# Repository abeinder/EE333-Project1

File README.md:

# EE333-Project1
EE design project for EE 333.

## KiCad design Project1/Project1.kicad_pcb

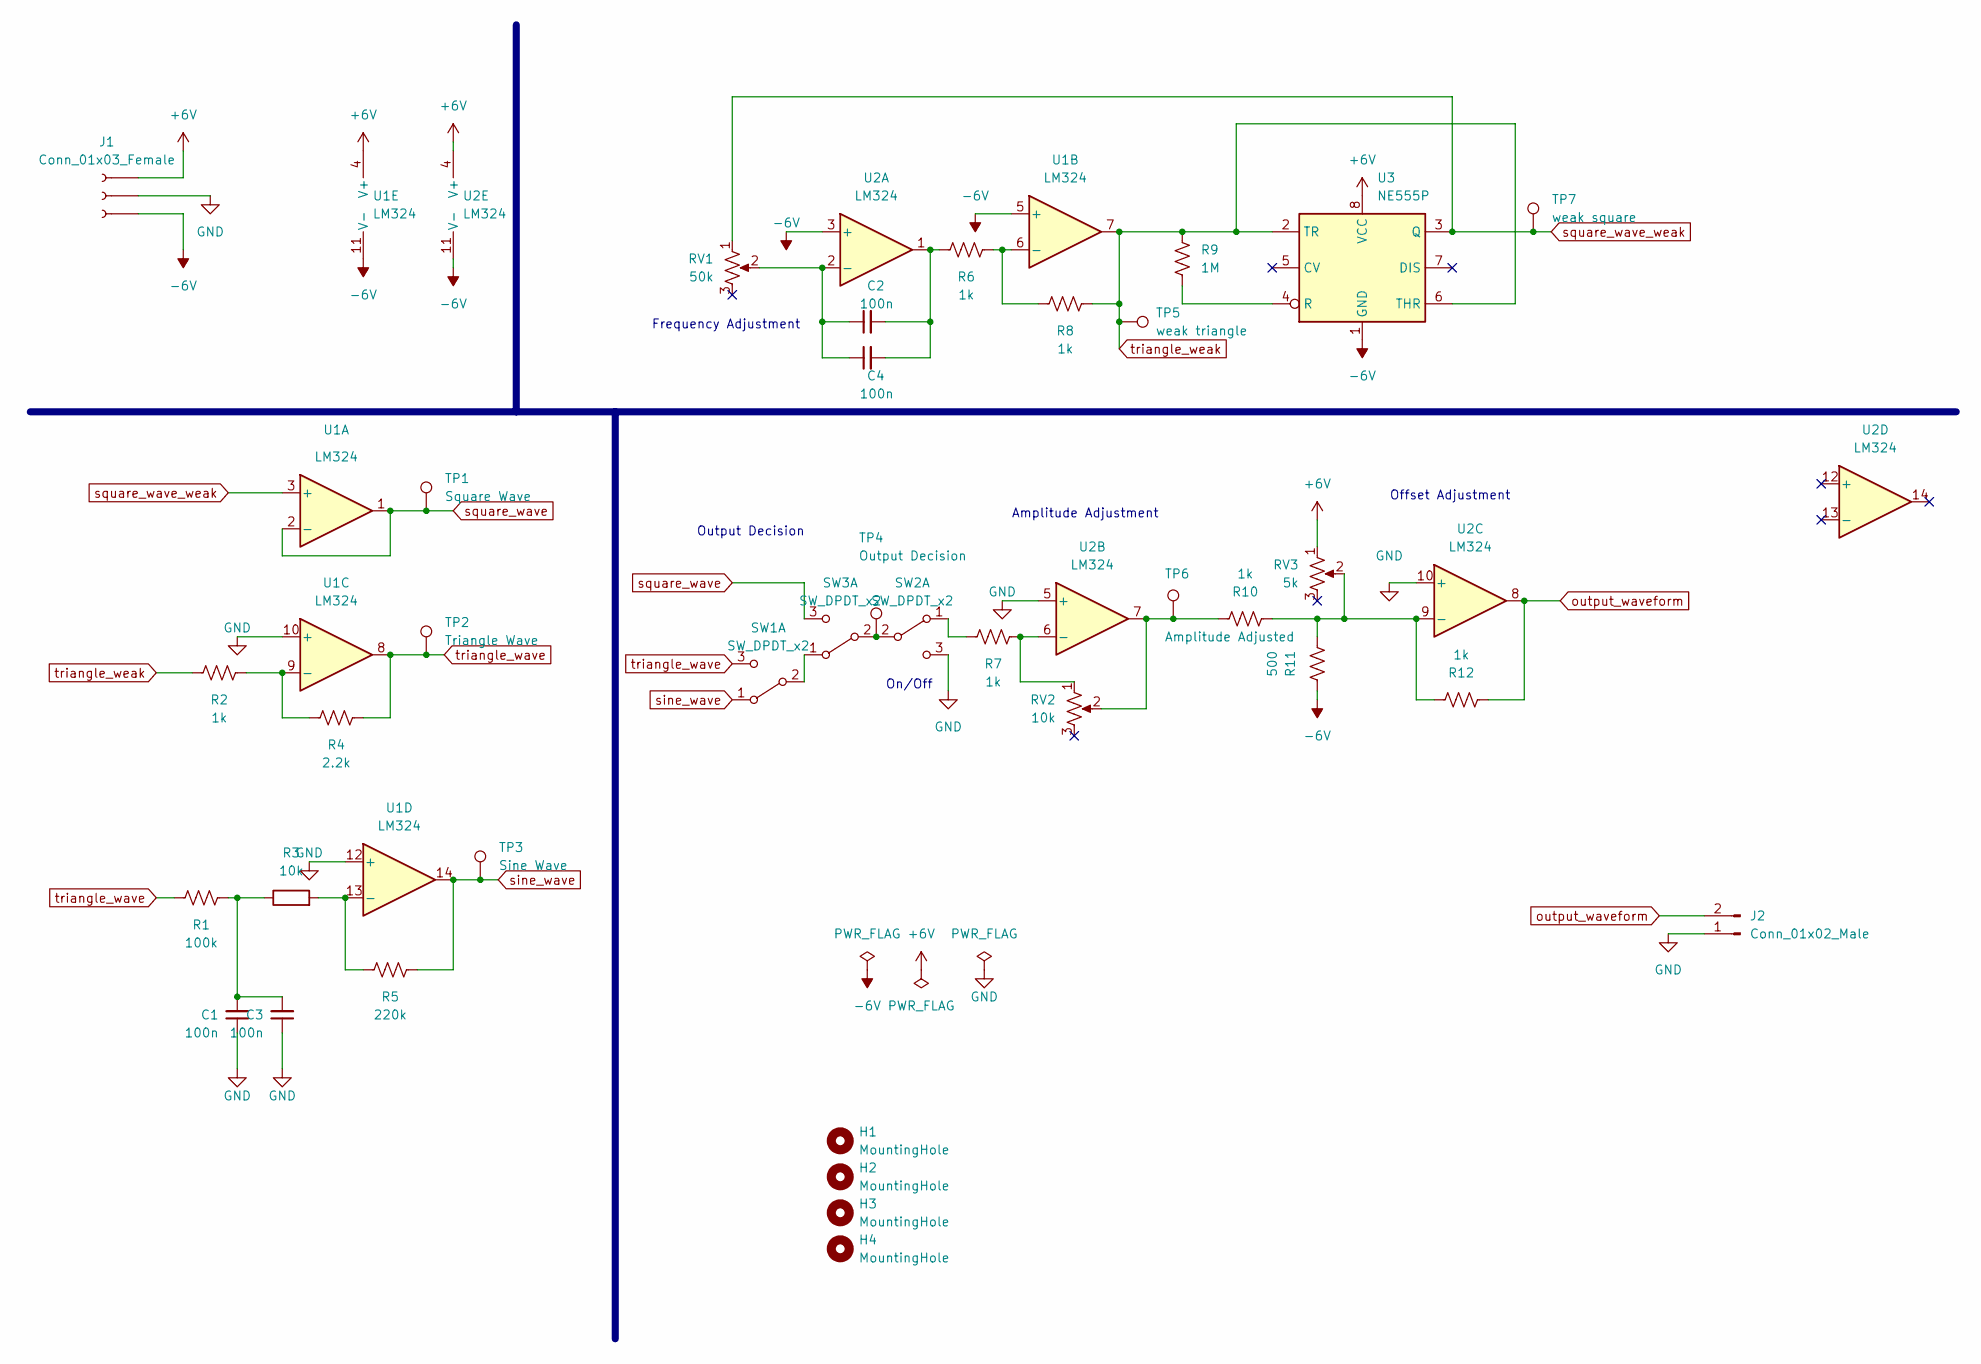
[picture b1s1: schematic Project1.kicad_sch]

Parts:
C1, C2, C3, C4: 100n; C_Rect_L7.0mm_W3.5mm_P5.00mm
H1, H2, H3, H4: MountingHole; MountingHole_5mm
J1: Conn_01x03_Female; PinSocket_1x03_P2.54mm_Vertical
J2: Conn_01x02_Male; PinSocket_1x02_P2.54mm_Vertical
R1: 100k; R_Axial_DIN0207_L6.3mm_D2.5mm_P7.62mm_Horizontal
R2, R6, R7, R8, R10, R12: 1k; R_Axial_DIN0207_L6.3mm_D2.5mm_P7.62mm_Horizontal
R3: 10k; R_Axial_DIN0207_L6.3mm_D2.5mm_P7.62mm_Horizontal
R4: 2.2k; R_Axial_DIN0207_L6.3mm_D2.5mm_P7.62mm_Horizontal
R5: 220k; R_Axial_DIN0207_L6.3mm_D2.5mm_P7.62mm_Horizontal
R9: 1M; R_Axial_DIN0207_L6.3mm_D2.5mm_P7.62mm_Horizontal
R11: 500; R_Axial_DIN0207_L6.3mm_D2.5mm_P7.62mm_Horizontal
RV1: 50k; Chomkypot
RV2: 10k; Chomkypot
RV3: 5k; Chomkypot
SW1, SW2, SW3: SW_DPDT_x2; PinSocket_1x03_P2.54mm_Vertical
TP1: Square Wave; TestPoint_Keystone_5010-5014_Multipurpose
TP2: Triangle Wave; TestPoint_Keystone_5010-5014_Multipurpose
TP3: Sine Wave; TestPoint_Keystone_5010-5014_Multipurpose
TP4: Output Decision; TestPoint_Keystone_5010-5014_Multipurpose
TP5: weak triangle; TestPoint_Keystone_5010-5014_Multipurpose
TP6: Amplitude Adjusted; TestPoint_Keystone_5010-5014_Multipurpose
TP7: weak square; TestPoint_Keystone_5010-5014_Multipurpose
U1, U2: LM324; DIP-14_W7.62mm_Socket_LongPads
U3: NE555P; DIP-8_W7.62mm_Socket_LongPads

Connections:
+6V: J1.3, RV3.1, U1.4 (V+), U2.4 (V+), U3.8 (VCC)
-6V: J1.1, R11.2, U1.5 (+), U1.11 (V-), U2.3 (+), U2.11 (V-), U3.1 (GND)
GND: C1.1, C3.1, J1.2, J2.1, SW2.3 (C), U1.10 (+), U1.12 (+), U2.5 (+), U2.10 (+)
unnamed: C1.2, C3.2, R1.2, R3.1
unnamed: C2.1, C4.1, RV1.2, U2.2 (-)
unnamed: C2.2, C4.2, R6.1, U2.1
unnamed: R2.2, R4.1, U1.9 (-)
unnamed: R3.2, R5.1, U1.13 (-)
unnamed: R6.2, R8.1, U1.6 (-)
unnamed: R7.1, SW2.1 (A)
unnamed: R7.2, RV2.1, U2.6 (-)
unnamed: R9.2, U3.4 (R)
unnamed: R10.1, R11.1, R12.2, RV3.2, U2.9 (-)
unnamed: R10.2, RV2.2, TP6.1, U2.7
unnamed: SW1.2 (B), SW3.1 (A)
unnamed: SW2.2 (B), SW3.2 (B), TP4.1
output_waveform: J2.2, R12.1, U2.8
sine_wave: R5.2, SW1.1 (A), TP3.1, U1.14
square_wave: SW3.3 (C), TP1.1, U1.1, U1.2 (-)
square_wave_weak: RV1.1, TP7.1, U1.3 (+), U3.3 (Q)
triangle_wave: R1.1, R4.2, SW1.3 (C), TP2.1, U1.8
triangle_weak: R2.1, R8.2, R9.1, TP5.1, U1.7, U3.2 (TR), U3.6 (THR)

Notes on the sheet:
On/Off
Frequency Adjustment
Output Decision
Amplitude Adjustment
Offset Adjustment

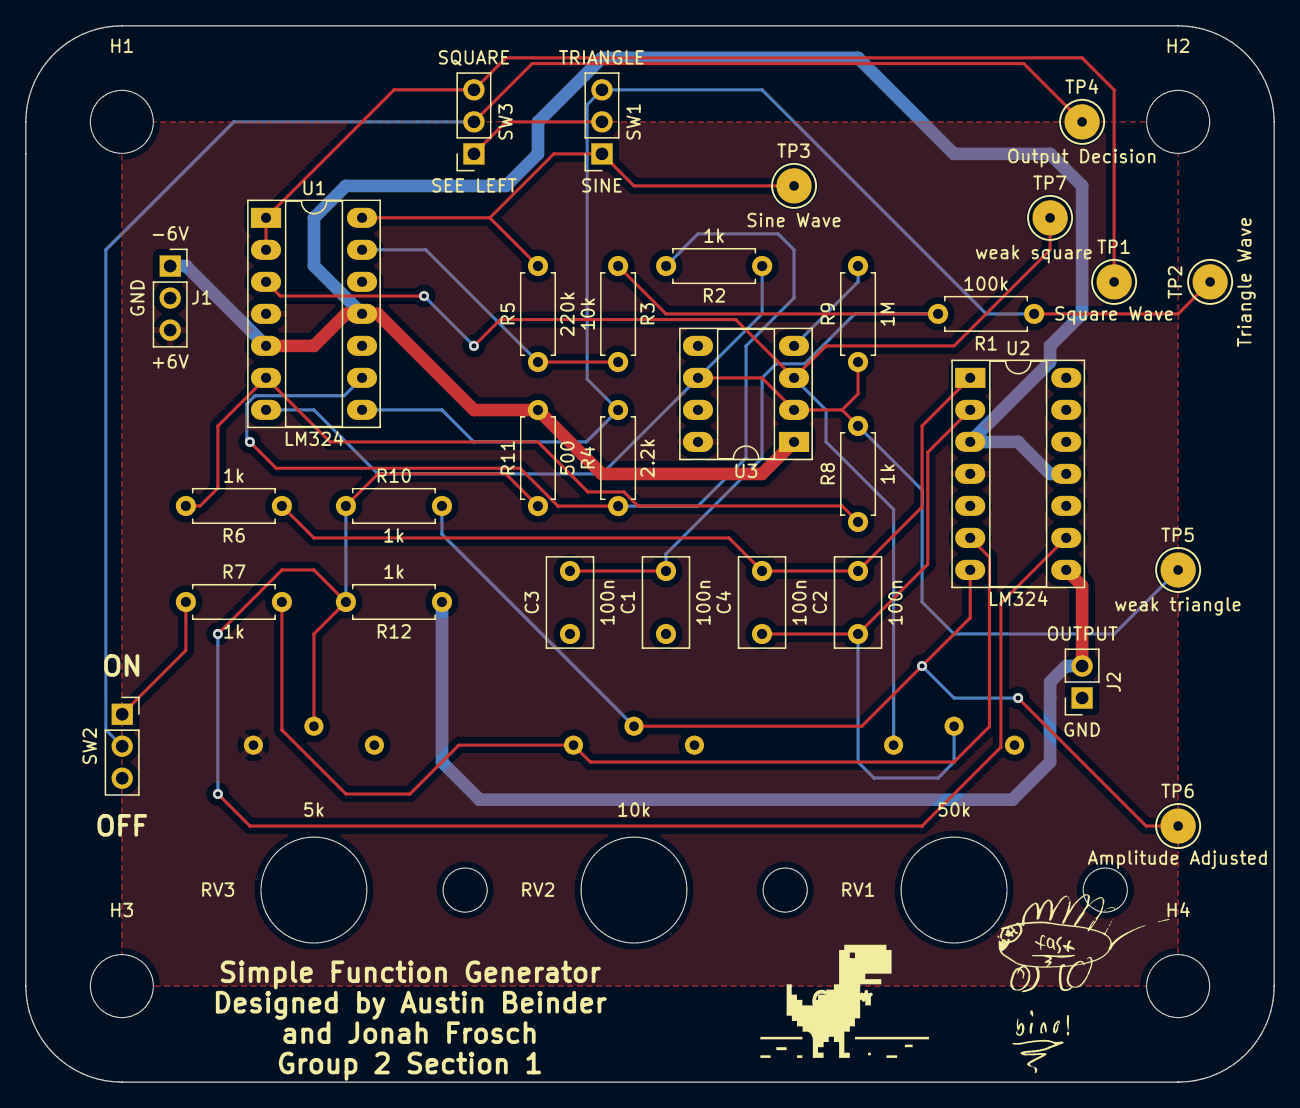
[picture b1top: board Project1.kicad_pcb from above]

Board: 2 copper layers, 99.1 x 83.8 mm, 38 parts (0 on the bottom side), 22 nets.

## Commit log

2022-08-29 Here be file
2022-08-29 changed file
2022-08-29 added Ne555
2022-08-30 Added start of BOM
2022-08-31 fixed resistor
2022-09-01 added some op amp and power amp stuff but the power amp doesn't work :(
2022-09-03 finished preliminary circuit and started BOM
2022-09-03 added bom desctriptions for missing components :)
2022-09-03 finished abstract, work needs to be done on part specifics
2022-09-10 tried to break power amp into its own schematic but its late and I'm kinda ready to go home
2022-09-15 began kicad design, tried to convert any components we had to being available in the lab kit. More work definitely needs to be done to ensure that we have the right footprints, and a proper bom put t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
2022-09-16 Finishing touches of PCB
2022-09-23 hiiiiiiiiiiii
2022-09-30 added switches and pot
2022-10-01 redesigned board
